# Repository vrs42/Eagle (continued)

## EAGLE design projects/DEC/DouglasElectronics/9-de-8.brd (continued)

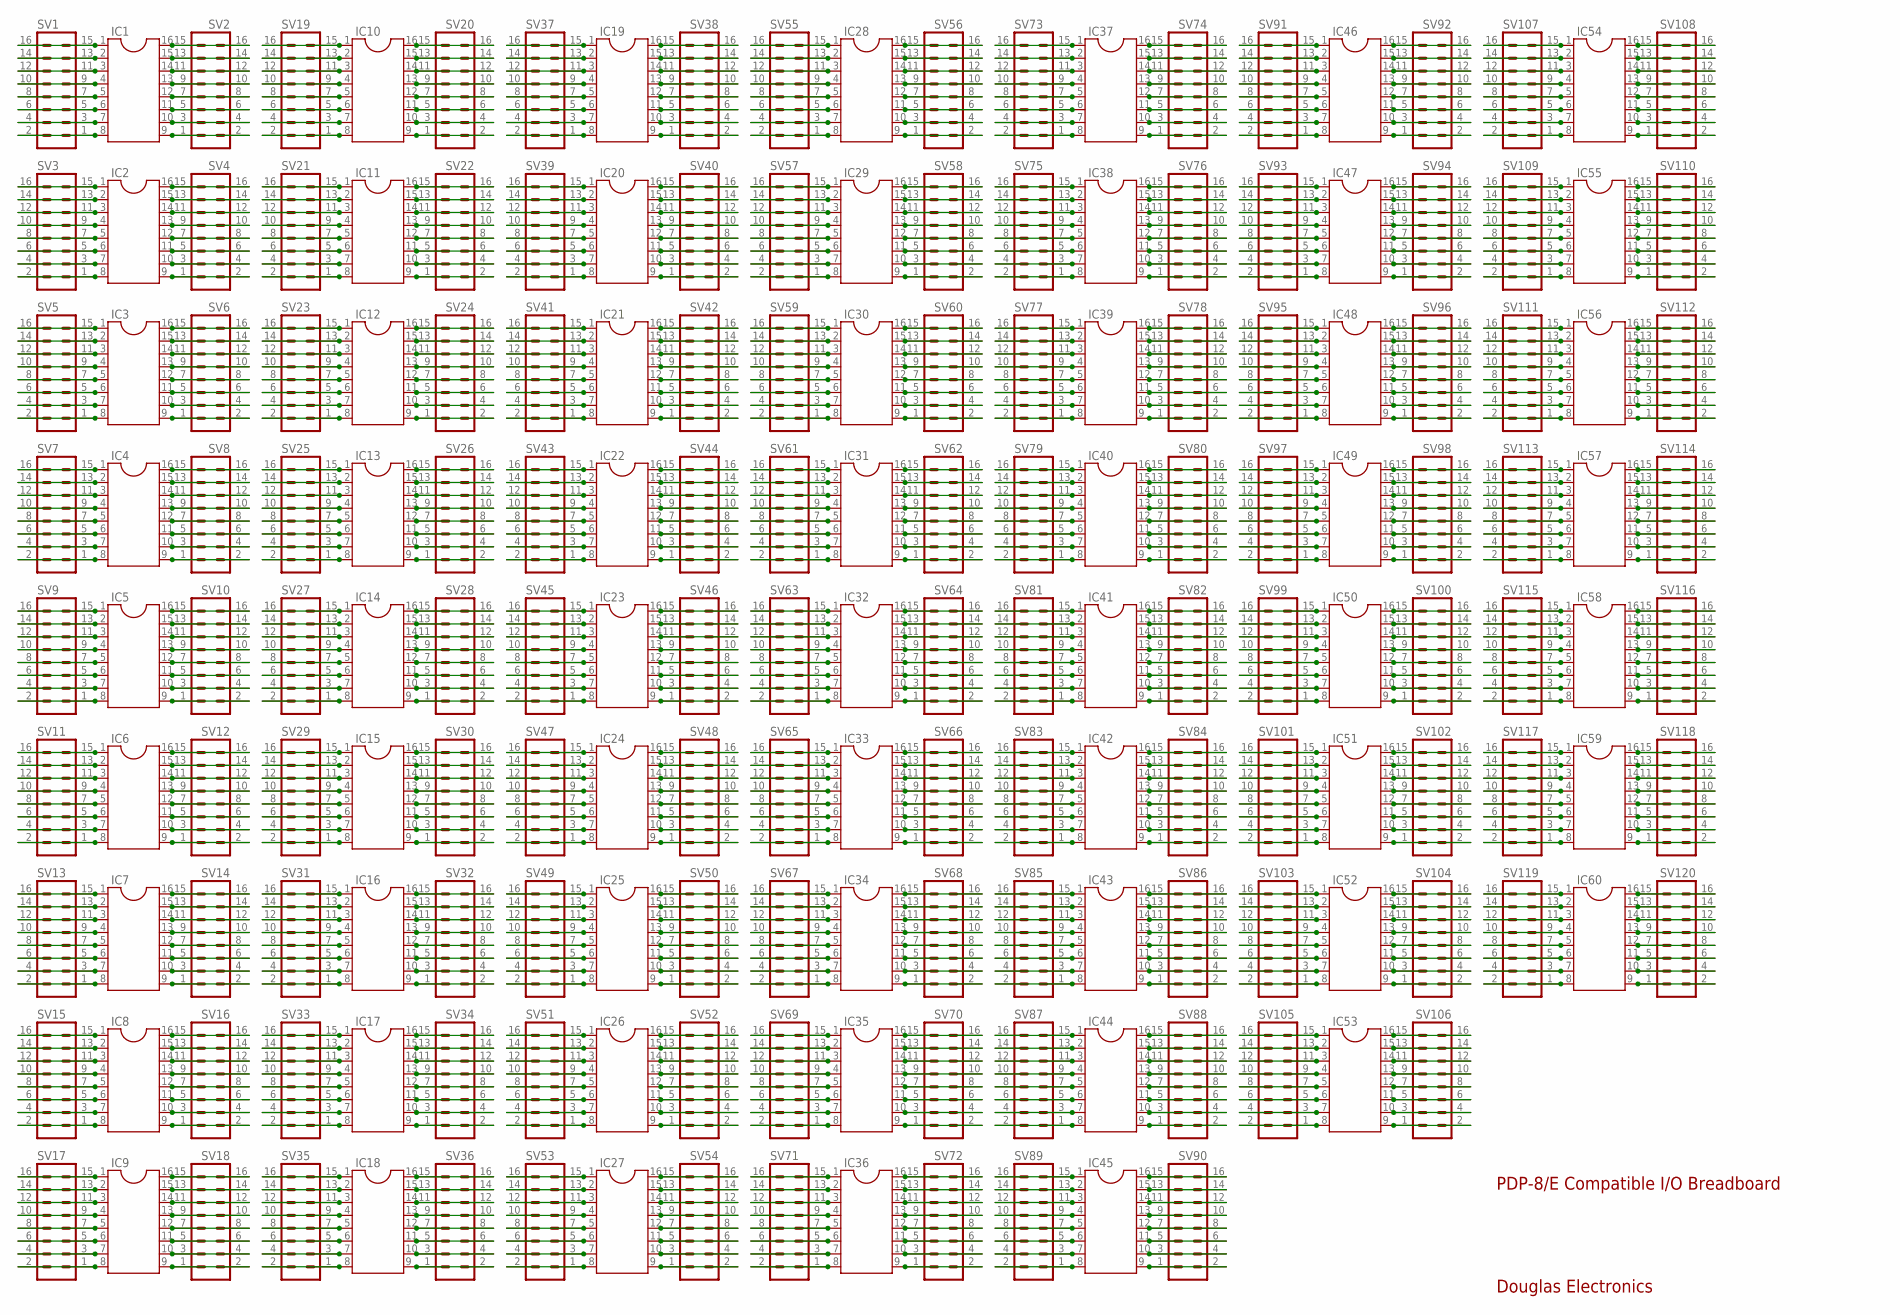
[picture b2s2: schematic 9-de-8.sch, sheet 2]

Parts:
IC1, IC2, IC3, IC4, IC5, IC6, IC7, IC8, IC9, IC10, IC11, IC12, IC13, IC14, IC15, IC16, IC17, IC18, IC19, IC20, IC21, IC22, IC23, IC24, IC25, IC26, IC27, IC28, IC29, IC30, IC31, IC32, IC33, IC34, IC35, IC36, IC37, IC38, IC39, IC40, IC41, IC42, IC43, IC44, IC45, IC46, IC47, IC48, IC49, IC50, IC51, IC52, IC53, IC54, IC55, IC56, IC57, IC58, IC59, IC60: DIL16
SV1, SV2, SV3, SV4, SV5, SV6, SV7, SV8, SV9, SV10, SV11, SV12, SV13, SV14, SV15, SV16, SV17, SV18, SV19, SV20, SV21, SV22, SV23, SV24, SV25, SV26, SV27, SV28, SV29, SV30, SV31, SV32, SV33, SV34, SV35, SV36, SV37, SV38, SV39, SV40, SV41, SV42, SV43, SV44, SV45, SV46, SV47, SV48, SV49, SV50, SV51, SV52, SV53, SV54, SV55, SV56, SV57, SV58, SV59, SV60, SV61, SV62, SV63, SV64, SV65, SV66, SV67, SV68, SV69, SV70, SV71, SV72, SV73, SV74, SV75, SV76, SV77, SV78, SV79, SV80, SV81, SV82, SV83, SV84, SV85, SV86, SV87, SV88, SV89, SV90, SV91, SV92, SV93, SV94, SV95, SV96, SV97, SV98, SV99, SV100, SV101, SV102, SV103, SV104, SV105, SV106, SV107, SV108, SV109, SV110, SV111, SV112, SV113, SV114, SV115, SV116, SV117, SV118, SV119, SV120: MA08-2

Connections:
unnamed: IC1.9, SV2.1, SV2.2
unnamed: IC1.10, SV2.3, SV2.4
unnamed: IC1.11, SV2.5, SV2.6
unnamed: IC1.12, SV2.7, SV2.8
unnamed: IC1.13, SV2.9, SV2.10
unnamed: IC1.14, SV2.11, SV2.12
unnamed: IC1.15, SV2.13, SV2.14
unnamed: IC1.16, SV2.15, SV2.16
unnamed: IC1.8, SV1.1, SV1.2
unnamed: IC2.9, SV4.1, SV4.2
unnamed: IC2.10, SV4.3, SV4.4
unnamed: IC2.11, SV4.5, SV4.6
unnamed: IC2.12, SV4.7, SV4.8
unnamed: IC2.13, SV4.9, SV4.10
unnamed: IC2.14, SV4.11, SV4.12
unnamed: IC2.15, SV4.13, SV4.14
unnamed: IC2.16, SV4.15, SV4.16
unnamed: IC2.8, SV3.1, SV3.2
unnamed: IC2.7, SV3.3, SV3.4
unnamed: IC2.6, SV3.5, SV3.6
unnamed: IC2.5, SV3.7, SV3.8
unnamed: IC2.4, SV3.9, SV3.10
unnamed: IC2.3, SV3.11, SV3.12
unnamed: IC2.2, SV3.13, SV3.14
unnamed: IC2.1, SV3.15, SV3.16
unnamed: IC1.7, SV1.3, SV1.4
unnamed: IC1.6, SV1.5, SV1.6
unnamed: IC1.5, SV1.7, SV1.8
unnamed: IC1.4, SV1.9, SV1.10
unnamed: IC3.9, SV6.1, SV6.2
unnamed: IC3.10, SV6.3, SV6.4
unnamed: IC3.11, SV6.5, SV6.6
unnamed: IC3.12, SV6.7, SV6.8
unnamed: IC3.13, SV6.9, SV6.10
unnamed: IC3.14, SV6.11, SV6.12
unnamed: IC3.15, SV6.13, SV6.14
unnamed: IC3.16, SV6.15, SV6.16
unnamed: IC3.8, SV5.1, SV5.2
unnamed: IC3.7, SV5.3, SV5.4
unnamed: IC3.6, SV5.5, SV5.6
unnamed: IC3.5, SV5.7, SV5.8
unnamed: IC3.4, SV5.9, SV5.10
unnamed: IC3.3, SV5.11, SV5.12
unnamed: IC3.2, SV5.13, SV5.14
unnamed: IC3.1, SV5.15, SV5.16
unnamed: IC4.9, SV8.1, SV8.2
unnamed: IC4.10, SV8.3, SV8.4
unnamed: IC4.11, SV8.5, SV8.6
unnamed: IC4.12, SV8.7, SV8.8
unnamed: IC4.13, SV8.9, SV8.10
unnamed: IC4.14, SV8.11, SV8.12
unnamed: IC4.15, SV8.13, SV8.14
unnamed: IC4.16, SV8.15, SV8.16
unnamed: IC4.8, SV7.1, SV7.2
unnamed: IC4.7, SV7.3, SV7.4
unnamed: IC4.6, SV7.5, SV7.6
unnamed: IC4.5, SV7.7, SV7.8
unnamed: IC4.4, SV7.9, SV7.10
unnamed: IC4.3, SV7.11, SV7.12
unnamed: IC4.2, SV7.13, SV7.14
unnamed: IC4.1, SV7.15, SV7.16
unnamed: IC5.9, SV10.1, SV10.2
unnamed: IC5.10, SV10.3, SV10.4
unnamed: IC5.11, SV10.5, SV10.6
unnamed: IC5.12, SV10.7, SV10.8
unnamed: IC5.13, SV10.9, SV10.10
unnamed: IC5.14, SV10.11, SV10.12
unnamed: IC5.15, SV10.13, SV10.14
unnamed: IC5.16, SV10.15, SV10.16
unnamed: IC5.8, SV9.1, SV9.2
unnamed: IC5.7, SV9.3, SV9.4
unnamed: IC5.6, SV9.5, SV9.6
unnamed: IC5.5, SV9.7, SV9.8
unnamed: IC5.4, SV9.9, SV9.10
unnamed: IC5.3, SV9.11, SV9.12
unnamed: IC5.2, SV9.13, SV9.14
unnamed: IC5.1, SV9.15, SV9.16
unnamed: IC6.9, SV12.1, SV12.2
unnamed: IC6.10, SV12.3, SV12.4
unnamed: IC6.11, SV12.5, SV12.6
unnamed: IC6.12, SV12.7, SV12.8
unnamed: IC6.13, SV12.9, SV12.10
unnamed: IC6.14, SV12.11, SV12.12
unnamed: IC6.15, SV12.13, SV12.14
unnamed: IC6.16, SV12.15, SV12.16
unnamed: IC6.8, SV11.1, SV11.2
unnamed: IC6.7, SV11.3, SV11.4
unnamed: IC6.6, SV11.5, SV11.6
unnamed: IC6.5, SV11.7, SV11.8
unnamed: IC6.4, SV11.9, SV11.10
unnamed: IC6.3, SV11.11, SV11.12
unnamed: IC6.2, SV11.13, SV11.14
unnamed: IC6.1, SV11.15, SV11.16
unnamed: IC7.9, SV14.1, SV14.2
unnamed: IC7.10, SV14.3, SV14.4
unnamed: IC7.11, SV14.5, SV14.6
unnamed: IC7.12, SV14.7, SV14.8
unnamed: IC7.13, SV14.9, SV14.10
unnamed: IC7.14, SV14.11, SV14.12
unnamed: IC7.15, SV14.13, SV14.14
unnamed: IC7.16, SV14.15, SV14.16
unnamed: IC7.8, SV13.1, SV13.2
unnamed: IC7.7, SV13.3, SV13.4
unnamed: IC7.6, SV13.5, SV13.6
unnamed: IC7.5, SV13.7, SV13.8
unnamed: IC7.4, SV13.9, SV13.10
unnamed: IC7.3, SV13.11, SV13.12
unnamed: IC7.2, SV13.13, SV13.14
unnamed: IC7.1, SV13.15, SV13.16
unnamed: IC8.9, SV16.1, SV16.2
unnamed: IC8.10, SV16.3, SV16.4
unnamed: IC8.11, SV16.5, SV16.6
unnamed: IC8.12, SV16.7, SV16.8
unnamed: IC8.13, SV16.9, SV16.10
unnamed: IC8.14, SV16.11, SV16.12
unnamed: IC8.15, SV16.13, SV16.14
unnamed: IC8.16, SV16.15, SV16.16
unnamed: IC8.8, SV15.1, SV15.2
unnamed: IC8.7, SV15.3, SV15.4
unnamed: IC8.6, SV15.5, SV15.6
unnamed: IC8.5, SV15.7, SV15.8
unnamed: IC8.4, SV15.9, SV15.10
unnamed: IC8.3, SV15.11, SV15.12
unnamed: IC8.2, SV15.13, SV15.14
unnamed: IC8.1, SV15.15, SV15.16
unnamed: IC9.9, SV18.1, SV18.2
unnamed: IC9.10, SV18.3, SV18.4
unnamed: IC9.11, SV18.5, SV18.6
unnamed: IC9.12, SV18.7, SV18.8
unnamed: IC9.13, SV18.9, SV18.10
unnamed: IC9.14, SV18.11, SV18.12
unnamed: IC9.15, SV18.13, SV18.14
unnamed: IC9.16, SV18.15, SV18.16
unnamed: IC9.8, SV17.1, SV17.2
unnamed: IC9.7, SV17.3, SV17.4
unnamed: IC9.6, SV17.5, SV17.6
unnamed: IC9.5, SV17.7, SV17.8
unnamed: IC9.4, SV17.9, SV17.10
unnamed: IC9.3, SV17.11, SV17.12
unnamed: IC9.2, SV17.13, SV17.14
unnamed: IC9.1, SV17.15, SV17.16
unnamed: IC10.9, SV20.1, SV20.2
unnamed: IC10.10, SV20.3, SV20.4
unnamed: IC10.11, SV20.5, SV20.6
unnamed: IC10.12, SV20.7, SV20.8
unnamed: IC10.13, SV20.9, SV20.10
unnamed: IC10.14, SV20.11, SV20.12
unnamed: IC10.15, SV20.13, SV20.14
unnamed: IC10.16, SV20.15, SV20.16
unnamed: IC10.8, SV19.1, SV19.2
unnamed: IC10.7, SV19.3, SV19.4
unnamed: IC10.6, SV19.5, SV19.6
unnamed: IC10.5, SV19.7, SV19.8
unnamed: IC10.4, SV19.9, SV19.10
unnamed: IC10.3, SV19.11, SV19.12
unnamed: IC10.2, SV19.13, SV19.14
unnamed: IC10.1, SV19.15, SV19.16
unnamed: IC11.9, SV22.1, SV22.2
unnamed: IC11.10, SV22.3, SV22.4
unnamed: IC11.11, SV22.5, SV22.6
unnamed: IC11.12, SV22.7, SV22.8
unnamed: IC11.13, SV22.9, SV22.10
unnamed: IC11.14, SV22.11, SV22.12
unnamed: IC11.15, SV22.13, SV22.14
unnamed: IC11.16, SV22.15, SV22.16
unnamed: IC11.8, SV21.1, SV21.2
unnamed: IC11.7, SV21.3, SV21.4
unnamed: IC11.6, SV21.5, SV21.6
unnamed: IC11.5, SV21.7, SV21.8
unnamed: IC11.4, SV21.9, SV21.10
unnamed: IC11.3, SV21.11, SV21.12
unnamed: IC11.2, SV21.13, SV21.14
unnamed: IC11.1, SV21.15, SV21.16
unnamed: IC12.9, SV24.1, SV24.2
unnamed: IC12.10, SV24.3, SV24.4
unnamed: IC12.11, SV24.5, SV24.6
unnamed: IC12.12, SV24.7, SV24.8
unnamed: IC12.13, SV24.9, SV24.10
unnamed: IC12.14, SV24.11, SV24.12
unnamed: IC12.15, SV24.13, SV24.14
unnamed: IC12.16, SV24.15, SV24.16
unnamed: IC12.8, SV23.1, SV23.2
unnamed: IC12.7, SV23.3, SV23.4
unnamed: IC12.6, SV23.5, SV23.6
unnamed: IC12.5, SV23.7, SV23.8
unnamed: IC12.4, SV23.9, SV23.10
unnamed: IC12.3, SV23.11, SV23.12
unnamed: IC12.2, SV23.13, SV23.14
unnamed: IC12.1, SV23.15, SV23.16
unnamed: IC13.9, SV26.1, SV26.2
unnamed: IC13.10, SV26.3, SV26.4
unnamed: IC13.11, SV26.5, SV26.6
unnamed: IC13.12, SV26.7, SV26.8
unnamed: IC13.13, SV26.9, SV26.10
unnamed: IC13.14, SV26.11, SV26.12
unnamed: IC13.15, SV26.13, SV26.14
unnamed: IC13.16, SV26.15, SV26.16
unnamed: IC13.8, SV25.1, SV25.2
unnamed: IC13.7, SV25.3, SV25.4
unnamed: IC13.6, SV25.5, SV25.6
unnamed: IC13.5, SV25.7, SV25.8
unnamed: IC13.4, SV25.9, SV25.10
unnamed: IC13.3, SV25.11, SV25.12
unnamed: IC13.2, SV25.13, SV25.14
unnamed: IC13.1, SV25.15, SV25.16
unnamed: IC14.9, SV28.1, SV28.2
unnamed: IC14.10, SV28.3, SV28.4
unnamed: IC14.11, SV28.5, SV28.6
unnamed: IC14.12, SV28.7, SV28.8
unnamed: IC14.13, SV28.9, SV28.10
unnamed: IC14.14, SV28.11, SV28.12
unnamed: IC14.15, SV28.13, SV28.14
unnamed: IC14.16, SV28.15, SV28.16
unnamed: IC14.8, SV27.1, SV27.2
unnamed: IC14.7, SV27.3, SV27.4
unnamed: IC14.6, SV27.5, SV27.6
unnamed: IC14.5, SV27.7, SV27.8
unnamed: IC14.4, SV27.9, SV27.10
unnamed: IC14.3, SV27.11, SV27.12
unnamed: IC14.2, SV27.13, SV27.14
unnamed: IC14.1, SV27.15, SV27.16
unnamed: IC15.9, SV30.1, SV30.2
unnamed: IC15.10, SV30.3, SV30.4
unnamed: IC15.11, SV30.5, SV30.6
unnamed: IC15.12, SV30.7, SV30.8
unnamed: IC15.13, SV30.9, SV30.10
unnamed: IC15.14, SV30.11, SV30.12
unnamed: IC15.15, SV30.13, SV30.14
unnamed: IC15.16, SV30.15, SV30.16
unnamed: IC15.8, SV29.1, SV29.2
unnamed: IC15.7, SV29.3, SV29.4
unnamed: IC15.6, SV29.5, SV29.6
unnamed: IC15.5, SV29.7, SV29.8
unnamed: IC15.4, SV29.9, SV29.10
unnamed: IC15.3, SV29.11, SV29.12
unnamed: IC15.2, SV29.13, SV29.14
unnamed: IC15.1, SV29.15, SV29.16
unnamed: IC16.9, SV32.1, SV32.2
unnamed: IC16.10, SV32.3, SV32.4
unnamed: IC16.11, SV32.5, SV32.6
unnamed: IC16.12, SV32.7, SV32.8
unnamed: IC16.13, SV32.9, SV32.10
unnamed: IC16.14, SV32.11, SV32.12
unnamed: IC16.15, SV32.13, SV32.14
unnamed: IC16.16, SV32.15, SV32.16
unnamed: IC16.8, SV31.1, SV31.2
unnamed: IC16.7, SV31.3, SV31.4
unnamed: IC16.6, SV31.5, SV31.6
unnamed: IC16.5, SV31.7, SV31.8
unnamed: IC16.4, SV31.9, SV31.10
unnamed: IC16.3, SV31.11, SV31.12
unnamed: IC16.2, SV31.13, SV31.14
unnamed: IC16.1, SV31.15, SV31.16
unnamed: IC17.9, SV34.1, SV34.2
unnamed: IC17.10, SV34.3, SV34.4
unnamed: IC17.11, SV34.5, SV34.6
unnamed: IC17.12, SV34.7, SV34.8
unnamed: IC17.13, SV34.9, SV34.10
unnamed: IC17.14, SV34.11, SV34.12
unnamed: IC17.15, SV34.13, SV34.14
unnamed: IC17.16, SV34.15, SV34.16
unnamed: IC17.8, SV33.1, SV33.2
unnamed: IC17.7, SV33.3, SV33.4
unnamed: IC17.6, SV33.5, SV33.6
unnamed: IC17.5, SV33.7, SV33.8
unnamed: IC17.4, SV33.9, SV33.10
unnamed: IC17.3, SV33.11, SV33.12
unnamed: IC17.2, SV33.13, SV33.14
unnamed: IC17.1, SV33.15, SV33.16
unnamed: IC18.9, SV36.1, SV36.2
unnamed: IC18.10, SV36.3, SV36.4
unnamed: IC18.11, SV36.5, SV36.6
unnamed: IC18.12, SV36.7, SV36.8
unnamed: IC18.13, SV36.9, SV36.10
unnamed: IC18.14, SV36.11, SV36.12
unnamed: IC18.15, SV36.13, SV36.14
unnamed: IC18.16, SV36.15, SV36.16
unnamed: IC18.8, SV35.1, SV35.2
unnamed: IC18.7, SV35.3, SV35.4
unnamed: IC18.6, SV35.5, SV35.6
unnamed: IC18.5, SV35.7, SV35.8
unnamed: IC18.4, SV35.9, SV35.10
unnamed: IC18.3, SV35.11, SV35.12
unnamed: IC18.2, SV35.13, SV35.14
unnamed: IC18.1, SV35.15, SV35.16
unnamed: IC19.9, SV38.1, SV38.2
unnamed: IC19.10, SV38.3, SV38.4
unnamed: IC19.11, SV38.5, SV38.6
unnamed: IC19.12, SV38.7, SV38.8
unnamed: IC19.13, SV38.9, SV38.10
unnamed: IC19.14, SV38.11, SV38.12
unnamed: IC19.15, SV38.13, SV38.14
unnamed: IC19.16, SV38.15, SV38.16
unnamed: IC19.8, SV37.1, SV37.2
unnamed: IC19.7, SV37.3, SV37.4
unnamed: IC19.6, SV37.5, SV37.6
unnamed: IC19.5, SV37.7, SV37.8
unnamed: IC19.4, SV37.9, SV37.10
unnamed: IC19.3, SV37.11, SV37.12
unnamed: IC19.2, SV37.13, SV37.14
unnamed: IC19.1, SV37.15, SV37.16
unnamed: IC20.9, SV40.1, SV40.2
unnamed: IC20.10, SV40.3, SV40.4
unnamed: IC20.11, SV40.5, SV40.6
unnamed: IC20.12, SV40.7, SV40.8
unnamed: IC20.13, SV40.9, SV40.10
unnamed: IC20.14, SV40.11, SV40.12
unnamed: IC20.15, SV40.13, SV40.14
unnamed: IC20.16, SV40.15, SV40.16
unnamed: IC20.8, SV39.1, SV39.2
unnamed: IC20.7, SV39.3, SV39.4
unnamed: IC20.6, SV39.5, SV39.6
unnamed: IC20.5, SV39.7, SV39.8
unnamed: IC20.4, SV39.9, SV39.10
unnamed: IC20.3, SV39.11, SV39.12
unnamed: IC20.2, SV39.13, SV39.14
unnamed: IC20.1, SV39.15, SV39.16
unnamed: IC21.9, SV42.1, SV42.2
unnamed: IC21.10, SV42.3, SV42.4
unnamed: IC21.11, SV42.5, SV42.6
unnamed: IC21.12, SV42.7, SV42.8
unnamed: IC21.13, SV42.9, SV42.10
unnamed: IC21.14, SV42.11, SV42.12
unnamed: IC21.15, SV42.13, SV42.14
unnamed: IC21.16, SV42.15, SV42.16
unnamed: IC21.8, SV41.1, SV41.2
unnamed: IC21.7, SV41.3, SV41.4
unnamed: IC21.6, SV41.5, SV41.6
unnamed: IC21.5, SV41.7, SV41.8
unnamed: IC21.4, SV41.9, SV41.10
unnamed: IC21.3, SV41.11, SV41.12
unnamed: IC21.2, SV41.13, SV41.14
unnamed: IC21.1, SV41.15, SV41.16
unnamed: IC22.9, SV44.1, SV44.2
unnamed: IC22.10, SV44.3, SV44.4
unnamed: IC22.11, SV44.5, SV44.6
unnamed: IC22.12, SV44.7, SV44.8
unnamed: IC22.13, SV44.9, SV44.10
unnamed: IC22.14, SV44.11, SV44.12
unnamed: IC22.15, SV44.13, SV44.14
unnamed: IC22.16, SV44.15, SV44.16
unnamed: IC22.8, SV43.1, SV43.2
unnamed: IC22.7, SV43.3, SV43.4
unnamed: IC22.6, SV43.5, SV43.6
unnamed: IC22.5, SV43.7, SV43.8
unnamed: IC22.4, SV43.9, SV43.10
unnamed: IC22.3, SV43.11, SV43.12
unnamed: IC22.2, SV43.13, SV43.14
unnamed: IC22.1, SV43.15, SV43.16
unnamed: IC23.9, SV46.1, SV46.2
unnamed: IC23.10, SV46.3, SV46.4
unnamed: IC23.11, SV46.5, SV46.6
unnamed: IC23.12, SV46.7, SV46.8
unnamed: IC23.13, SV46.9, SV46.10
unnamed: IC23.14, SV46.11, SV46.12
unnamed: IC23.15, SV46.13, SV46.14
unnamed: IC23.16, SV46.15, SV46.16
unnamed: IC23.8, SV45.1, SV45.2
unnamed: IC23.7, SV45.3, SV45.4
unnamed: IC23.6, SV45.5, SV45.6
unnamed: IC23.5, SV45.7, SV45.8
unnamed: IC23.4, SV45.9, SV45.10
unnamed: IC23.3, SV45.11, SV45.12
unnamed: IC23.2, SV45.13, SV45.14
unnamed: IC23.1, SV45.15, SV45.16
unnamed: IC24.9, SV48.1, SV48.2
unnamed: IC24.10, SV48.3, SV48.4
unnamed: IC24.11, SV48.5, SV48.6
unnamed: IC24.12, SV48.7, SV48.8
unnamed: IC24.13, SV48.9, SV48.10
unnamed: IC24.14, SV48.11, SV48.12
unnamed: IC24.15, SV48.13, SV48.14
unnamed: IC24.16, SV48.15, SV48.16
unnamed: IC24.8, SV47.1, SV47.2
unnamed: IC24.7, SV47.3, SV47.4
unnamed: IC24.6, SV47.5, SV47.6
unnamed: IC24.5, SV47.7, SV47.8
unnamed: IC24.4, SV47.9, SV47.10
unnamed: IC24.3, SV47.11, SV47.12
unnamed: IC24.2, SV47.13, SV47.14
unnamed: IC24.1, SV47.15, SV47.16
unnamed: IC25.9, SV50.1, SV50.2
unnamed: IC25.10, SV50.3, SV50.4
unnamed: IC25.11, SV50.5, SV50.6
unnamed: IC25.12, SV50.7, SV50.8
unnamed: IC25.13, SV50.9, SV50.10
unnamed: IC25.14, SV50.11, SV50.12
unnamed: IC25.15, SV50.13, SV50.14
unnamed: IC25.16, SV50.15, SV50.16
unnamed: IC25.8, SV49.1, SV49.2
unnamed: IC25.7, SV49.3, SV49.4
unnamed: IC25.6, SV49.5, SV49.6
unnamed: IC25.5, SV49.7, SV49.8
unnamed: IC25.4, SV49.9, SV49.10
unnamed: IC25.3, SV49.11, SV49.12
unnamed: IC25.2, SV49.13, SV49.14
unnamed: IC25.1, SV49.15, SV49.16
unnamed: IC26.9, SV52.1, SV52.2
unnamed: IC26.10, SV52.3, SV52.4
unnamed: IC26.11, SV52.5, SV52.6
unnamed: IC26.12, SV52.7, SV52.8
unnamed: IC26.13, SV52.9, SV52.10
unnamed: IC26.14, SV52.11, SV52.12
unnamed: IC26.15, SV52.13, SV52.14
unnamed: IC26.16, SV52.15, SV52.16
unnamed: IC26.8, SV51.1, SV51.2
unnamed: IC26.7, SV51.3, SV51.4
unnamed: IC26.6, SV51.5, SV51.6
unnamed: IC26.5, SV51.7, SV51.8
unnamed: IC26.4, SV51.9, SV51.10
unnamed: IC26.3, SV51.11, SV51.12
unnamed: IC26.2, SV51.13, SV51.14
unnamed: IC26.1, SV51.15, SV51.16
unnamed: IC27.9, SV54.1, SV54.2
unnamed: IC27.10, SV54.3, SV54.4
unnamed: IC27.11, SV54.5, SV54.6
unnamed: IC27.12, SV54.7, SV54.8
unnamed: IC27.13, SV54.9, SV54.10
unnamed: IC27.14, SV54.11, SV54.12
unnamed: IC27.15, SV54.13, SV54.14
unnamed: IC27.16, SV54.15, SV54.16
unnamed: IC27.8, SV53.1, SV53.2
unnamed: IC27.7, SV53.3, SV53.4
unnamed: IC27.6, SV53.5, SV53.6
unnamed: IC27.5, SV53.7, SV53.8
unnamed: IC27.4, SV53.9, SV53.10
unnamed: IC27.3, SV53.11, SV53.12
unnamed: IC27.2, SV53.13, SV53.14
unnamed: IC27.1, SV53.15, SV53.16
unnamed: IC28.9, SV56.1, SV56.2
unnamed: IC28.10, SV56.3, SV56.4
unnamed: IC28.11, SV56.5, SV56.6
unnamed: IC28.12, SV56.7, SV56.8
unnamed: IC28.13, SV56.9, SV56.10
unnamed: IC28.14, SV56.11, SV56.12
unnamed: IC28.15, SV56.13, SV56.14
unnamed: IC28.16, SV56.15, SV56.16
unnamed: IC28.8, SV55.1, SV55.2
unnamed: IC28.7, SV55.3, SV55.4
unnamed: IC28.6, SV55.5, SV55.6
unnamed: IC28.5, SV55.7, SV55.8
unnamed: IC28.4, SV55.9, SV55.10
unnamed: IC28.3, SV55.11, SV55.12
unnamed: IC28.2, SV55.13, SV55.14
unnamed: IC28.1, SV55.15, SV55.16
unnamed: IC29.9, SV58.1, SV58.2
unnamed: IC29.10, SV58.3, SV58.4
unnamed: IC29.11, SV58.5, SV58.6
unnamed: IC29.12, SV58.7, SV58.8
unnamed: IC1.3, SV1.11, SV1.12
unnamed: IC1.2, SV1.13, SV1.14
unnamed: IC1.1, SV1.15, SV1.16
unnamed: IC29.13, SV58.9, SV58.10
unnamed: IC29.14, SV58.11, SV58.12
unnamed: IC29.15, SV58.13, SV58.14
unnamed: IC29.16, SV58.15, SV58.16
unnamed: IC29.8, SV57.1, SV57.2
unnamed: IC29.7, SV57.3, SV57.4
unnamed: IC29.6, SV57.5, SV57.6
unnamed: IC29.5, SV57.7, SV57.8
unnamed: IC29.4, SV57.9, SV57.10
unnamed: IC29.3, SV57.11, SV57.12
unnamed: IC29.2, SV57.13, SV57.14
unnamed: IC29.1, SV57.15, SV57.16
unnamed: IC30.9, SV60.1, SV60.2
unnamed: IC30.10, SV60.3, SV60.4
unnamed: IC30.11, SV60.5, SV60.6
unnamed: IC30.12, SV60.7, SV60.8
unnamed: IC30.13, SV60.9, SV60.10
unnamed: IC30.14, SV60.11, SV60.12
unnamed: IC30.15, SV60.13, SV60.14
unnamed: IC30.16, SV60.15, SV60.16
unnamed: IC30.8, SV59.1, SV59.2
unnamed: IC30.7, SV59.3, SV59.4
unnamed: IC30.6, SV59.5, SV59.6
unnamed: IC30.5, SV59.7, SV59.8
unnamed: IC30.4, SV59.9, SV59.10
unnamed: IC30.3, SV59.11, SV59.12
unnamed: IC30.2, SV59.13, SV59.14
unnamed: IC30.1, SV59.15, SV59.16
unnamed: IC31.9, SV62.1, SV62.2
unnamed: IC31.10, SV62.3, SV62.4
unnamed: IC31.11, SV62.5, SV62.6
unnamed: IC31.12, SV62.7, SV62.8
unnamed: IC31.13, SV62.9, SV62.10
unnamed: IC31.14, SV62.11, SV62.12
unnamed: IC31.15, SV62.13, SV62.14
unnamed: IC31.16, SV62.15, SV62.16
unnamed: IC31.8, SV61.1, SV61.2
unnamed: IC31.7, SV61.3, SV61.4
unnamed: IC31.6, SV61.5, SV61.6
unnamed: IC31.5, SV61.7, SV61.8
unnamed: IC31.4, SV61.9, SV61.10
unnamed: IC31.3, SV61.11, SV61.12
unnamed: IC31.2, SV61.13, SV61.14
unnamed: IC31.1, SV61.15, SV61.16
unnamed: IC32.9, SV64.1, SV64.2
unnamed: IC32.10, SV64.3, SV64.4
unnamed: IC32.11, SV64.5, SV64.6
unnamed: IC32.12, SV64.7, SV64.8
unnamed: IC32.13, SV64.9, SV64.10
unnamed: IC32.14, SV64.11, SV64.12
unnamed: IC32.15, SV64.13, SV64.14
unnamed: IC32.16, SV64.15, SV64.16
unnamed: IC32.8, SV63.1, SV63.2
unnamed: IC32.7, SV63.3, SV63.4
unnamed: IC32.6, SV63.5, SV63.6
unnamed: IC32.5, SV63.7, SV63.8
unnamed: IC32.4, SV63.9, SV63.10
unnamed: IC32.3, SV63.11, SV63.12
unnamed: IC32.2, SV63.13, SV63.14
unnamed: IC32.1, SV63.15, SV63.16
unnamed: IC33.9, SV66.1, SV66.2
unnamed: IC33.10, SV66.3, SV66.4
unnamed: IC33.11, SV66.5, SV66.6
unnamed: IC33.12, SV66.7, SV66.8
unnamed: IC33.13, SV66.9, SV66.10
unnamed: IC33.14, SV66.11, SV66.12
unnamed: IC33.15, SV66.13, SV66.14
unnamed: IC33.16, SV66.15, SV66.16
unnamed: IC33.8, SV65.1, SV65.2
unnamed: IC33.7, SV65.3, SV65.4
unnamed: IC33.6, SV65.5, SV65.6
unnamed: IC33.5, SV65.7, SV65.8
unnamed: IC33.4, SV65.9, SV65.10
unnamed: IC33.3, SV65.11, SV65.12
unnamed: IC33.2, SV65.13, SV65.14
unnamed: IC33.1, SV65.15, SV65.16
unnamed: IC34.9, SV68.1, SV68.2
unnamed: IC34.10, SV68.3, SV68.4
unnamed: IC34.11, SV68.5, SV68.6
unnamed: IC34.12, SV68.7, SV68.8
unnamed: IC34.13, SV68.9, SV68.10
unnamed: IC34.14, SV68.11, SV68.12
unnamed: IC34.15, SV68.13, SV68.14
unnamed: IC34.16, SV68.15, SV68.16
unnamed: IC34.8, SV67.1, SV67.2
unnamed: IC34.7, SV67.3, SV67.4
unnamed: IC34.6, SV67.5, SV67.6
unnamed: IC34.5, SV67.7, SV67.8
unnamed: IC34.4, SV67.9, SV67.10
unnamed: IC34.3, SV67.11, SV67.12
unnamed: IC34.2, SV67.13, SV67.14
unnamed: IC34.1, SV67.15, SV67.16
unnamed: IC35.9, SV70.1, SV70.2
unnamed: IC35.10, SV70.3, SV70.4
unnamed: IC35.11, SV70.5, SV70.6
unnamed: IC35.12, SV70.7, SV70.8
unnamed: IC35.13, SV70.9, SV70.10
unnamed: IC35.14, SV70.11, SV70.12
unnamed: IC35.15, SV70.13, SV70.14
unnamed: IC35.16, SV70.15, SV70.16
unnamed: IC35.8, SV69.1, SV69.2
unnamed: IC35.7, SV69.3, SV69.4
unnamed: IC35.6, SV69.5, SV69.6
unnamed: IC35.5, SV69.7, SV69.8
unnamed: IC35.4, SV69.9, SV69.10
unnamed: IC35.3, SV69.11, SV69.12
unnamed: IC35.2, SV69.13, SV69.14
unnamed: IC35.1, SV69.15, SV69.16
unnamed: IC36.9, SV72.1, SV72.2
unnamed: IC36.10, SV72.3, SV72.4
unnamed: IC36.11, SV72.5, SV72.6
unnamed: IC36.12, SV72.7, SV72.8
unnamed: IC36.13, SV72.9, SV72.10
unnamed: IC36.14, SV72.11, SV72.12
unnamed: IC36.15, SV72.13, SV72.14
unnamed: IC36.16, SV72.15, SV72.16
unnamed: IC36.8, SV71.1, SV71.2
unnamed: IC36.7, SV71.3, SV71.4
unnamed: IC36.6, SV71.5, SV71.6
unnamed: IC36.5, SV71.7, SV71.8
unnamed: IC36.4, SV71.9, SV71.10
unnamed: IC36.3, SV71.11, SV71.12
unnamed: IC36.2, SV71.13, SV71.14
unnamed: IC36.1, SV71.15, SV71.16
unnamed: IC37.9, SV74.1, SV74.2
unnamed: IC37.10, SV74.3, SV74.4
unnamed: IC37.11, SV74.5, SV74.6
unnamed: IC37.12, SV74.7, SV74.8
unnamed: IC37.13, SV74.9, SV74.10
unnamed: IC37.14, SV74.11, SV74.12
unnamed: IC37.15, SV74.13, SV74.14
unnamed: IC37.16, SV74.15, SV74.16
unnamed: IC37.8, SV73.1, SV73.2
unnamed: IC37.7, SV73.3, SV73.4
unnamed: IC37.6, SV73.5, SV73.6
unnamed: IC37.5, SV73.7, SV73.8
unnamed: IC37.4, SV73.9, SV73.10
unnamed: IC37.3, SV73.11, SV73.12
unnamed: IC37.2, SV73.13, SV73.14
unnamed: IC37.1, SV73.15, SV73.16
unnamed: IC38.9, SV76.1, SV76.2
unnamed: IC38.10, SV76.3, SV76.4
unnamed: IC38.11, SV76.5, SV76.6
unnamed: IC38.12, SV76.7, SV76.8
unnamed: IC38.13, SV76.9, SV76.10
unnamed: IC38.14, SV76.11, SV76.12
unnamed: IC38.15, SV76.13, SV76.14
unnamed: IC38.16, SV76.15, SV76.16
unnamed: IC38.8, SV75.1, SV75.2
unnamed: IC38.7, SV75.3, SV75.4
unnamed: IC38.6, SV75.5, SV75.6
unnamed: IC38.5, SV75.7, SV75.8
unnamed: IC38.4, SV75.9, SV75.10
unnamed: IC38.3, SV75.11, SV75.12
unnamed: IC38.2, SV75.13, SV75.14
unnamed: IC38.1, SV75.15, SV75.16
unnamed: IC39.9, SV78.1, SV78.2
unnamed: IC39.10, SV78.3, SV78.4
unnamed: IC39.11, SV78.5, SV78.6
unnamed: IC39.12, SV78.7, SV78.8
unnamed: IC39.13, SV78.9, SV78.10
unnamed: IC39.14, SV78.11, SV78.12
unnamed: IC39.15, SV78.13, SV78.14
unnamed: IC39.16, SV78.15, SV78.16
unnamed: IC39.8, SV77.1, SV77.2
unnamed: IC39.7, SV77.3, SV77.4
unnamed: IC39.6, SV77.5, SV77.6
unnamed: IC39.5, SV77.7, SV77.8
unnamed: IC39.4, SV77.9, SV77.10
unnamed: IC39.3, SV77.11, SV77.12
unnamed: IC39.2, SV77.13, SV77.14
unnamed: IC39.1, SV77.15, SV77.16
unnamed: IC40.9, SV80.1, SV80.2
unnamed: IC40.10, SV80.3, SV80.4
unnamed: IC40.11, SV80.5, SV80.6
unnamed: IC40.12, SV80.7, SV80.8
unnamed: IC40.13, SV80.9, SV80.10
unnamed: IC40.14, SV80.11, SV80.12
unnamed: IC40.15, SV80.13, SV80.14
unnamed: IC40.16, SV80.15, SV80.16
unnamed: IC40.8, SV79.1, SV79.2
unnamed: IC40.7, SV79.3, SV79.4
unnamed: IC40.6, SV79.5, SV79.6
unnamed: IC40.5, SV79.7, SV79.8
unnamed: IC40.4, SV79.9, SV79.10
unnamed: IC40.3, SV79.11, SV79.12
unnamed: IC40.2, SV79.13, SV79.14
unnamed: IC40.1, SV79.15, SV79.16
unnamed: IC41.9, SV82.1, SV82.2
unnamed: IC41.10, SV82.3, SV82.4
unnamed: IC41.11, SV82.5, SV82.6
unnamed: IC41.12, SV82.7, SV82.8
unnamed: IC41.13, SV82.9, SV82.10
unnamed: IC41.14, SV82.11, SV82.12
unnamed: IC41.15, SV82.13, SV82.14
unnamed: IC41.16, SV82.15, SV82.16
unnamed: IC41.8, SV81.1, SV81.2
unnamed: IC41.7, SV81.3, SV81.4
unnamed: IC41.6, SV81.5, SV81.6
unnamed: IC41.5, SV81.7, SV81.8
unnamed: IC41.4, SV81.9, SV81.10
unnamed: IC41.3, SV81.11, SV81.12
unnamed: IC41.2, SV81.13, SV81.14
unnamed: IC41.1, SV81.15, SV81.16
unnamed: IC42.9, SV84.1, SV84.2
unnamed: IC42.10, SV84.3, SV84.4
unnamed: IC42.11, SV84.5, SV84.6
unnamed: IC42.12, SV84.7, SV84.8
unnamed: IC42.13, SV84.9, SV84.10
unnamed: IC42.14, SV84.11, SV84.12
unnamed: IC42.15, SV84.13, SV84.14
unnamed: IC42.16, SV84.15, SV84.16
unnamed: IC42.8, SV83.1, SV83.2
unnamed: IC42.7, SV83.3, SV83.4
unnamed: IC42.6, SV83.5, SV83.6
unnamed: IC42.5, SV83.7, SV83.8
unnamed: IC42.4, SV83.9, SV83.10
unnamed: IC42.3, SV83.11, SV83.12
unnamed: IC42.2, SV83.13, SV83.14
unnamed: IC42.1, SV83.15, SV83.16
unnamed: IC43.9, SV86.1, SV86.2
unnamed: IC43.10, SV86.3, SV86.4
unnamed: IC43.11, SV86.5, SV86.6
unnamed: IC43.12, SV86.7, SV86.8
unnamed: IC43.13, SV86.9, SV86.10
unnamed: IC43.14, SV86.11, SV86.12
unnamed: IC43.15, SV86.13, SV86.14
unnamed: IC43.16, SV86.15, SV86.16
unnamed: IC43.8, SV85.1, SV85.2
unnamed: IC43.7, SV85.3, SV85.4
unnamed: IC43.6, SV85.5, SV85.6
unnamed: IC43.5, SV85.7, SV85.8
unnamed: IC43.4, SV85.9, SV85.10
unnamed: IC43.3, SV85.11, SV85.12
unnamed: IC43.2, SV85.13, SV85.14
unnamed: IC43.1, SV85.15, SV85.16
unnamed: IC44.9, SV88.1, SV88.2
unnamed: IC44.10, SV88.3, SV88.4
unnamed: IC44.11, SV88.5, SV88.6
unnamed: IC44.12, SV88.7, SV88.8
unnamed: IC44.13, SV88.9, SV88.10
unnamed: IC44.14, SV88.11, SV88.12
unnamed: IC44.15, SV88.13, SV88.14
unnamed: IC44.16, SV88.15, SV88.16
unnamed: IC44.8, SV87.1, SV87.2
unnamed: IC44.7, SV87.3, SV87.4
unnamed: IC44.6, SV87.5, SV87.6
unnamed: IC44.5, SV87.7, SV87.8
unnamed: IC44.4, SV87.9, SV87.10
unnamed: IC44.3, SV87.11, SV87.12
unnamed: IC44.2, SV87.13, SV87.14
unnamed: IC44.1, SV87.15, SV87.16
unnamed: IC45.9, SV90.1, SV90.2
unnamed: IC45.10, SV90.3, SV90.4
unnamed: IC45.11, SV90.5, SV90.6
unnamed: IC45.12, SV90.7, SV90.8
unnamed: IC45.13, SV90.9, SV90.10
unnamed: IC45.14, SV90.11, SV90.12
unnamed: IC45.15, SV90.13, SV90.14
unnamed: IC45.16, SV90.15, SV90.16
unnamed: IC45.8, SV89.1, SV89.2
unnamed: IC45.7, SV89.3, SV89.4
unnamed: IC45.6, SV89.5, SV89.6
unnamed: IC45.5, SV89.7, SV89.8
unnamed: IC45.4, SV89.9, SV89.10
unnamed: IC45.3, SV89.11, SV89.12
unnamed: IC45.2, SV89.13, SV89.14
unnamed: IC45.1, SV89.15, SV89.16
unnamed: IC46.9, SV92.1, SV92.2
unnamed: IC46.10, SV92.3, SV92.4
unnamed: IC46.11, SV92.5, SV92.6
unnamed: IC46.12, SV92.7, SV92.8
unnamed: IC46.13, SV92.9, SV92.10
unnamed: IC46.14, SV92.11, SV92.12
unnamed: IC46.15, SV92.13, SV92.14
unnamed: IC46.16, SV92.15, SV92.16
unnamed: IC46.8, SV91.1, SV91.2
unnamed: IC46.7, SV91.3, SV91.4
unnamed: IC46.6, SV91.5, SV91.6
unnamed: IC46.5, SV91.7, SV91.8
unnamed: IC46.4, SV91.9, SV91.10
unnamed: IC46.3, SV91.11, SV91.12
unnamed: IC46.2, SV91.13, SV91.14
unnamed: IC46.1, SV91.15, SV91.16
unnamed: IC47.9, SV94.1, SV94.2
unnamed: IC47.10, SV94.3, SV94.4
unnamed: IC47.11, SV94.5, SV94.6
unnamed: IC47.12, SV94.7, SV94.8
unnamed: IC47.13, SV94.9, SV94.10
unnamed: IC47.14, SV94.11, SV94.12
unnamed: IC47.15, SV94.13, SV94.14
unnamed: IC47.16, SV94.15, SV94.16
unnamed: IC47.8, SV93.1, SV93.2
unnamed: IC47.7, SV93.3, SV93.4
unnamed: IC47.6, SV93.5, SV93.6
unnamed: IC47.5, SV93.7, SV93.8
unnamed: IC47.4, SV93.9, SV93.10
unnamed: IC47.3, SV93.11, SV93.12
unnamed: IC47.2, SV93.13, SV93.14
unnamed: IC47.1, SV93.15, SV93.16
unnamed: IC48.9, SV96.1, SV96.2
unnamed: IC48.10, SV96.3, SV96.4
unnamed: IC48.11, SV96.5, SV96.6
unnamed: IC48.12, SV96.7, SV96.8
unnamed: IC48.13, SV96.9, SV96.10
unnamed: IC48.14, SV96.11, SV96.12
unnamed: IC48.15, SV96.13, SV96.14
unnamed: IC48.16, SV96.15, SV96.16
unnamed: IC48.8, SV95.1, SV95.2
unnamed: IC48.7, SV95.3, SV95.4
unnamed: IC48.6, SV95.5, SV95.6
unnamed: IC48.5, SV95.7, SV95.8
unnamed: IC48.4, SV95.9, SV95.10
unnamed: IC48.3, SV95.11, SV95.12
unnamed: IC48.2, SV95.13, SV95.14
unnamed: IC48.1, SV95.15, SV95.16
unnamed: IC49.9, SV98.1, SV98.2
unnamed: IC49.10, SV98.3, SV98.4
unnamed: IC49.11, SV98.5, SV98.6
unnamed: IC49.12, SV98.7, SV98.8
unnamed: IC49.13, SV98.9, SV98.10
unnamed: IC49.14, SV98.11, SV98.12
unnamed: IC49.15, SV98.13, SV98.14
unnamed: IC49.16, SV98.15, SV98.16
unnamed: IC49.8, SV97.1, SV97.2
unnamed: IC49.7, SV97.3, SV97.4
unnamed: IC49.6, SV97.5, SV97.6
unnamed: IC49.5, SV97.7, SV97.8
unnamed: IC49.4, SV97.9, SV97.10
unnamed: IC49.3, SV97.11, SV97.12
unnamed: IC49.2, SV97.13, SV97.14
unnamed: IC49.1, SV97.15, SV97.16
unnamed: IC50.9, SV100.1, SV100.2
unnamed: IC50.10, SV100.3, SV100.4
unnamed: IC50.11, SV100.5, SV100.6
unnamed: IC50.12, SV100.7, SV100.8
unnamed: IC50.13, SV100.9, SV100.10
unnamed: IC50.14, SV100.11, SV100.12
unnamed: IC50.15, SV100.13, SV100.14
unnamed: IC50.16, SV100.15, SV100.16
unnamed: IC50.8, SV99.1, SV99.2
unnamed: IC50.7, SV99.3, SV99.4
unnamed: IC50.6, SV99.5, SV99.6
unnamed: IC50.5, SV99.7, SV99.8
unnamed: IC50.4, SV99.9, SV99.10
unnamed: IC50.3, SV99.11, SV99.12
unnamed: IC50.2, SV99.13, SV99.14
unnamed: IC50.1, SV99.15, SV99.16
unnamed: IC51.9, SV102.1, SV102.2
unnamed: IC51.10, SV102.3, SV102.4
unnamed: IC51.11, SV102.5, SV102.6
unnamed: IC51.12, SV102.7, SV102.8
unnamed: IC51.13, SV102.9, SV102.10
unnamed: IC51.14, SV102.11, SV102.12
unnamed: IC51.15, SV102.13, SV102.14
unnamed: IC51.16, SV102.15, SV102.16
unnamed: IC51.8, SV101.1, SV101.2
unnamed: IC51.7, SV101.3, SV101.4
unnamed: IC51.6, SV101.5, SV101.6
unnamed: IC51.5, SV101.7, SV101.8
unnamed: IC51.4, SV101.9, SV101.10
unnamed: IC51.3, SV101.11, SV101.12
unnamed: IC51.2, SV101.13, SV101.14
unnamed: IC51.1, SV101.15, SV101.16
unnamed: IC52.9, SV104.1, SV104.2
unnamed: IC52.10, SV104.3, SV104.4
unnamed: IC52.11, SV104.5, SV104.6
unnamed: IC52.12, SV104.7, SV104.8
unnamed: IC52.13, SV104.9, SV104.10
unnamed: IC52.14, SV104.11, SV104.12
unnamed: IC52.15, SV104.13, SV104.14
unnamed: IC52.16, SV104.15, SV104.16
unnamed: IC52.8, SV103.1, SV103.2
unnamed: IC52.7, SV103.3, SV103.4
unnamed: IC52.6, SV103.5, SV103.6
unnamed: IC52.5, SV103.7, SV103.8
unnamed: IC52.4, SV103.9, SV103.10
unnamed: IC52.3, SV103.11, SV103.12
unnamed: IC52.2, SV103.13, SV103.14
unnamed: IC52.1, SV103.15, SV103.16
unnamed: IC53.9, SV106.1, SV106.2
unnamed: IC53.10, SV106.3, SV106.4
unnamed: IC53.11, SV106.5, SV106.6
unnamed: IC53.12, SV106.7, SV106.8
unnamed: IC53.13, SV106.9, SV106.10
unnamed: IC53.14, SV106.11, SV106.12
unnamed: IC53.15, SV106.13, SV106.14
unnamed: IC53.16, SV106.15, SV106.16
unnamed: IC53.8, SV105.1, SV105.2
unnamed: IC53.7, SV105.3, SV105.4
unnamed: IC53.6, SV105.5, SV105.6
unnamed: IC53.5, SV105.7, SV105.8
unnamed: IC53.4, SV105.9, SV105.10
unnamed: IC53.3, SV105.11, SV105.12
unnamed: IC53.2, SV105.13, SV105.14
unnamed: IC53.1, SV105.15, SV105.16
unnamed: IC54.9, SV108.1, SV108.2
unnamed: IC54.10, SV108.3, SV108.4
unnamed: IC54.11, SV108.5, SV108.6
unnamed: IC54.12, SV108.7, SV108.8
unnamed: IC54.13, SV108.9, SV108.10
unnamed: IC54.14, SV108.11, SV108.12
unnamed: IC54.15, SV108.13, SV108.14
unnamed: IC54.16, SV108.15, SV108.16
unnamed: IC54.8, SV107.1, SV107.2
unnamed: IC54.7, SV107.3, SV107.4
unnamed: IC54.6, SV107.5, SV107.6
unnamed: IC54.5, SV107.7, SV107.8
unnamed: IC54.4, SV107.9, SV107.10
unnamed: IC54.3, SV107.11, SV107.12
unnamed: IC54.2, SV107.13, SV107.14
unnamed: IC54.1, SV107.15, SV107.16
unnamed: IC55.9, SV110.1, SV110.2
unnamed: IC55.10, SV110.3, SV110.4
unnamed: IC55.11, SV110.5, SV110.6
unnamed: IC55.12, SV110.7, SV110.8
unnamed: IC55.13, SV110.9, SV110.10
unnamed: IC55.14, SV110.11, SV110.12
unnamed: IC55.15, SV110.13, SV110.14
unnamed: IC55.16, SV110.15, SV110.16
unnamed: IC55.8, SV109.1, SV109.2
unnamed: IC55.7, SV109.3, SV109.4
unnamed: IC55.6, SV109.5, SV109.6
unnamed: IC55.5, SV109.7, SV109.8
unnamed: IC55.4, SV109.9, SV109.10
unnamed: IC55.3, SV109.11, SV109.12
unnamed: IC55.2, SV109.13, SV109.14
unnamed: IC55.1, SV109.15, SV109.16
unnamed: IC56.9, SV112.1, SV112.2
unnamed: IC56.10, SV112.3, SV112.4
unnamed: IC56.11, SV112.5, SV112.6
unnamed: IC56.12, SV112.7, SV112.8
unnamed: IC56.13, SV112.9, SV112.10
unnamed: IC56.14, SV112.11, SV112.12
unnamed: IC56.15, SV112.13, SV112.14
unnamed: IC56.16, SV112.15, SV112.16
unnamed: IC56.8, SV111.1, SV111.2
unnamed: IC56.7, SV111.3, SV111.4
unnamed: IC56.6, SV111.5, SV111.6
unnamed: IC56.5, SV111.7, SV111.8
unnamed: IC56.4, SV111.9, SV111.10
unnamed: IC56.3, SV111.11, SV111.12
unnamed: IC56.2, SV111.13, SV111.14
unnamed: IC56.1, SV111.15, SV111.16
unnamed: IC57.9, SV114.1, SV114.2
unnamed: IC57.10, SV114.3, SV114.4
unnamed: IC57.11, SV114.5, SV114.6
unnamed: IC57.12, SV114.7, SV114.8
unnamed: IC57.13, SV114.9, SV114.10
unnamed: IC57.14, SV114.11, SV114.12
unnamed: IC57.15, SV114.13, SV114.14
unnamed: IC57.16, SV114.15, SV114.16
unnamed: IC57.8, SV113.1, SV113.2
unnamed: IC57.7, SV113.3, SV113.4
unnamed: IC57.6, SV113.5, SV113.6
unnamed: IC57.5, SV113.7, SV113.8
unnamed: IC57.4, SV113.9, SV113.10
unnamed: IC57.3, SV113.11, SV113.12
unnamed: IC57.2, SV113.13, SV113.14
unnamed: IC57.1, SV113.15, SV113.16
unnamed: IC58.9, SV116.1, SV116.2
unnamed: IC58.10, SV116.3, SV116.4
unnamed: IC58.11, SV116.5, SV116.6
unnamed: IC58.12, SV116.7, SV116.8
unnamed: IC58.13, SV116.9, SV116.10
unnamed: IC58.14, SV116.11, SV116.12
unnamed: IC58.15, SV116.13, SV116.14
unnamed: IC58.16, SV116.15, SV116.16
unnamed: IC58.8, SV115.1, SV115.2
unnamed: IC58.7, SV115.3, SV115.4
unnamed: IC58.6, SV115.5, SV115.6
unnamed: IC58.5, SV115.7, SV115.8
unnamed: IC58.4, SV115.9, SV115.10
unnamed: IC58.3, SV115.11, SV115.12
unnamed: IC58.2, SV115.13, SV115.14
unnamed: IC58.1, SV115.15, SV115.16
unnamed: IC59.9, SV118.1, SV118.2
unnamed: IC59.10, SV118.3, SV118.4
unnamed: IC59.11, SV118.5, SV118.6
unnamed: IC59.12, SV118.7, SV118.8
unnamed: IC59.13, SV118.9, SV118.10
unnamed: IC59.14, SV118.11, SV118.12
unnamed: IC59.15, SV118.13, SV118.14
unnamed: IC59.16, SV118.15, SV118.16
unnamed: IC59.8, SV117.1, SV117.2
unnamed: IC59.7, SV117.3, SV117.4
unnamed: IC59.6, SV117.5, SV117.6
unnamed: IC59.5, SV117.7, SV117.8
unnamed: IC59.4, SV117.9, SV117.10
unnamed: IC59.3, SV117.11, SV117.12
unnamed: IC59.2, SV117.13, SV117.14
unnamed: IC59.1, SV117.15, SV117.16
unnamed: IC60.9, SV120.1, SV120.2
unnamed: IC60.10, SV120.3, SV120.4
unnamed: IC60.11, SV120.5, SV120.6
unnamed: IC60.12, SV120.7, SV120.8
unnamed: IC60.13, SV120.9, SV120.10
unnamed: IC60.14, SV120.11, SV120.12
unnamed: IC60.15, SV120.13, SV120.14
unnamed: IC60.16, SV120.15, SV120.16
unnamed: IC60.8, SV119.1, SV119.2
unnamed: IC60.7, SV119.3, SV119.4
unnamed: IC60.6, SV119.5, SV119.6
unnamed: IC60.5, SV119.7, SV119.8
unnamed: IC60.4, SV119.9, SV119.10
unnamed: IC60.3, SV119.11, SV119.12
unnamed: IC60.2, SV119.13, SV119.14
unnamed: IC60.1, SV119.15, SV119.16

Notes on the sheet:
PDP-8/E Compatible I/O Breadboard
Douglas Electronics
